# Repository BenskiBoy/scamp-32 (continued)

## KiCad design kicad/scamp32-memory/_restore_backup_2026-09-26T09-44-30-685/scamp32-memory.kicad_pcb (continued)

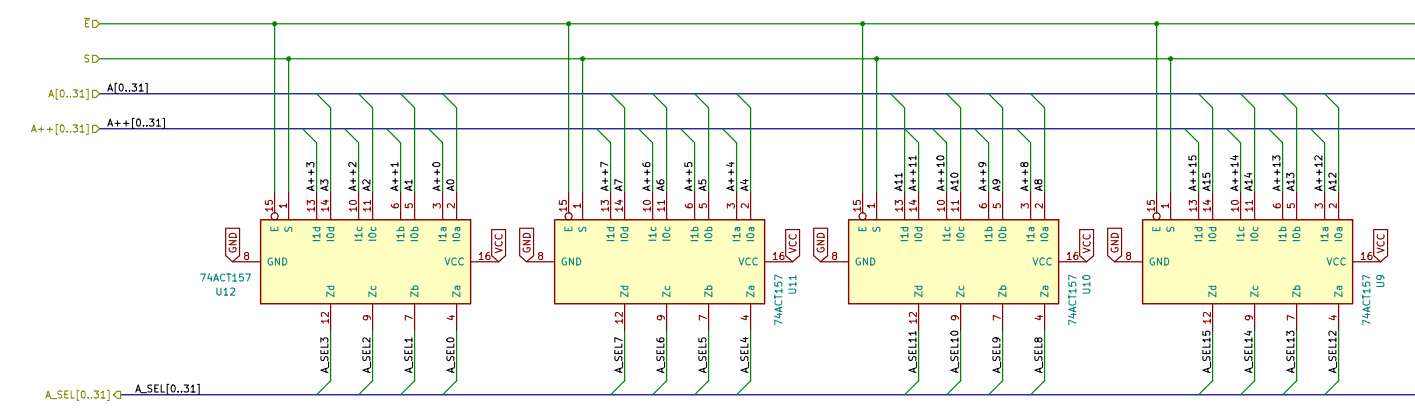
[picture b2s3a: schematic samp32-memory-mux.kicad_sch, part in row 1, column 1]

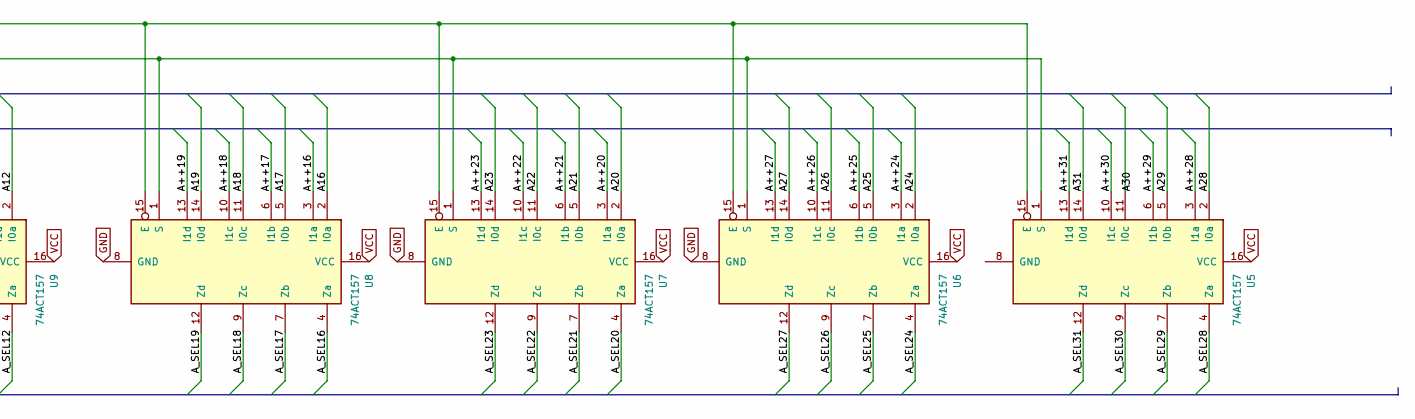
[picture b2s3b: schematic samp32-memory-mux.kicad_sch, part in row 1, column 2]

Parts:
U5, U6, U7, U8, U9, U10, U11, U12: 74ACT157; TSSOP-16_4.4x5mm_P0.65mm

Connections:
/A0: U12.2 (I0a); also elsewhere on the board
/A1: U12.5 (I0b); also elsewhere on the board
/A2: U12.11 (I0c); also elsewhere on the board
/A3: U12.14 (I0d); also elsewhere on the board
/A4: U11.2 (I0a); also elsewhere on the board
/A5: U11.5 (I0b); also elsewhere on the board
/A6: U11.11 (I0c); also elsewhere on the board
/A7: U11.14 (I0d); also elsewhere on the board
/A8: U10.2 (I0a); also elsewhere on the board
/A9: U10.5 (I0b); also elsewhere on the board
/A10: U10.11 (I0c); also elsewhere on the board
/A11: U10.13 (I1d); also elsewhere on the board
/A12: U9.2 (I0a); also elsewhere on the board
/A13: U9.5 (I0b); also elsewhere on the board
/A14: U9.11 (I0c); also elsewhere on the board
/A15: U9.14 (I0d); also elsewhere on the board
/A16: U8.2 (I0a); also elsewhere on the board
/A17: U8.5 (I0b); also elsewhere on the board
/A18: U8.11 (I0c); also elsewhere on the board
/A19: U8.14 (I0d); also elsewhere on the board
/A20: U7.2 (I0a); also elsewhere on the board
/A21: U7.5 (I0b); also elsewhere on the board
/A22: U7.11 (I0c); also elsewhere on the board
/A23: U7.14 (I0d); also elsewhere on the board
/A24: U6.2 (I0a); also elsewhere on the board
/A25: U6.5 (I0b); also elsewhere on the board
/A26: U6.11 (I0c); also elsewhere on the board
/A27: U6.14 (I0d); also elsewhere on the board
/A28: U5.2 (I0a); also elsewhere on the board
/A29: U5.5 (I0b); also elsewhere on the board
/A31: U5.14 (I0d); also elsewhere on the board
/samp32-memory-mux/A++0: U12.3 (I1a); also elsewhere on the board
/samp32-memory-mux/A++1: U12.6 (I1b); also elsewhere on the board
/samp32-memory-mux/A++2: U12.10 (I1c); also elsewhere on the board
/samp32-memory-mux/A++3: U12.13 (I1d); also elsewhere on the board
/samp32-memory-mux/A++4: U11.3 (I1a); also elsewhere on the board
/samp32-memory-mux/A++5: U11.6 (I1b); also elsewhere on the board
/samp32-memory-mux/A++6: U11.10 (I1c); also elsewhere on the board
/samp32-memory-mux/A++7: U11.13 (I1d); also elsewhere on the board
/samp32-memory-mux/A++8: U10.3 (I1a); also elsewhere on the board
/samp32-memory-mux/A++9: U10.6 (I1b); also elsewhere on the board
/samp32-memory-mux/A++10: U10.10 (I1c); also elsewhere on the board
/samp32-memory-mux/A++11: U10.14 (I0d); also elsewhere on the board
/samp32-memory-mux/A++12: U9.3 (I1a); also elsewhere on the board
/samp32-memory-mux/A++13: U9.6 (I1b); also elsewhere on the board
/samp32-memory-mux/A++14: U9.10 (I1c); also elsewhere on the board
/samp32-memory-mux/A++15: U9.13 (I1d); also elsewhere on the board
/samp32-memory-mux/A++16: U8.3 (I1a); also elsewhere on the board
/samp32-memory-mux/A++17: U8.6 (I1b); also elsewhere on the board
/samp32-memory-mux/A++18: U8.10 (I1c); also elsewhere on the board
/samp32-memory-mux/A++19: U8.13 (I1d); also elsewhere on the board
/samp32-memory-mux/A++20: U7.3 (I1a); also elsewhere on the board
/samp32-memory-mux/A++21: U7.6 (I1b); also elsewhere on the board
/samp32-memory-mux/A++22: U7.10 (I1c); also elsewhere on the board
/samp32-memory-mux/A++23: U7.13 (I1d); also elsewhere on the board
/samp32-memory-mux/A++24: U6.3 (I1a); also elsewhere on the board
/samp32-memory-mux/A++25: U6.6 (I1b); also elsewhere on the board
/samp32-memory-mux/A++26: U6.10 (I1c); also elsewhere on the board
/samp32-memory-mux/A++27: U6.13 (I1d); also elsewhere on the board
/samp32-memory-mux/A++28: U5.3 (I1a); also elsewhere on the board
/samp32-memory-mux/A++29: U5.6 (I1b); also elsewhere on the board
/samp32-memory-mux/A++30: U5.10 (I1c); also elsewhere on the board
/samp32-memory-mux/A++31: U5.13 (I1d); also elsewhere on the board
/samp32-memory-mux/A_SEL0: U12.4 (Za); also elsewhere on the board
/samp32-memory-mux/A_SEL1: U12.7 (Zb); also elsewhere on the board
/samp32-memory-mux/A_SEL2: U12.9 (Zc); also elsewhere on the board
/samp32-memory-mux/A_SEL3: U12.12 (Zd); also elsewhere on the board
/samp32-memory-mux/A_SEL4: U11.4 (Za); also elsewhere on the board
/samp32-memory-mux/A_SEL5: U11.7 (Zb); also elsewhere on the board
/samp32-memory-mux/A_SEL6: U11.9 (Zc); also elsewhere on the board
/samp32-memory-mux/A_SEL7: U11.12 (Zd); also elsewhere on the board
/samp32-memory-mux/A_SEL8: U10.4 (Za); also elsewhere on the board
/samp32-memory-mux/A_SEL9: U10.7 (Zb); also elsewhere on the board
/samp32-memory-mux/A_SEL10: U10.9 (Zc); also elsewhere on the board
/samp32-memory-mux/A_SEL11: U10.12 (Zd); also elsewhere on the board
/samp32-memory-mux/A_SEL12: U9.4 (Za); also elsewhere on the board
/samp32-memory-mux/A_SEL13: U9.7 (Zb); also elsewhere on the board
/samp32-memory-mux/A_SEL14: U9.9 (Zc); also elsewhere on the board
/samp32-memory-mux/A_SEL15: U9.12 (Zd); also elsewhere on the board
/samp32-memory-mux/A_SEL16: U8.4 (Za); also elsewhere on the board
/samp32-memory-mux/A_SEL17: U8.7 (Zb); also elsewhere on the board
/samp32-memory-mux/A_SEL18: U8.9 (Zc); also elsewhere on the board
/samp32-memory-mux/A_SEL19: U8.12 (Zd)
/samp32-memory-mux/A_SEL20: U7.4 (Za)
/samp32-memory-mux/A_SEL21: U7.7 (Zb)
/samp32-memory-mux/A_SEL22: U7.9 (Zc)
/samp32-memory-mux/A_SEL23: U7.12 (Zd)
/samp32-memory-mux/A_SEL24: U6.4 (Za)
/samp32-memory-mux/A_SEL25: U6.7 (Zb)
/samp32-memory-mux/A_SEL26: U6.9 (Zc)
/samp32-memory-mux/A_SEL27: U6.12 (Zd)
/samp32-memory-mux/A_SEL28: U5.4 (Za)
/samp32-memory-mux/A_SEL29: U5.7 (Zb)
/samp32-memory-mux/A_SEL30: U5.9 (Zc)
/samp32-memory-mux/A_SEL31: U5.12 (Zd)
/samp32-memory-mux/S: U5.1 (S), U6.1 (S), U7.1 (S), U8.1 (S), U9.1 (S), U10.1 (S), U11.1 (S), U12.1 (S); also elsewhere on the board
GND: U5.15 (E), U6.8 (GND), U6.15 (E), U7.8 (GND), U7.15 (E), U8.8 (GND), U8.15 (E), U9.8 (GND), U9.15 (E), U10.8 (GND), U10.15 (E), U11.8 (GND), U11.15 (E), U12.8 (GND), U12.15 (E); also elsewhere on the board
VCC: U5.16 (VCC), U6.16 (VCC), U7.16 (VCC), U8.16 (VCC), U9.16 (VCC), U10.16 (VCC), U11.16 (VCC), U12.16 (VCC); also elsewhere on the board

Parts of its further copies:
U13, U14, U15, U16, U17, U18, U19, U20: 74ACT157; TSSOP-16_4.4x5mm_P0.65mm

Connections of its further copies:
/A0: U13.2 (I0a); also elsewhere on the board
/A1: U13.5 (I0b); also elsewhere on the board
/A2: U13.11 (I0c); also elsewhere on the board
/A3: U13.14 (I0d); also elsewhere on the board
/A4: U14.2 (I0a); also elsewhere on the board
/A5: U14.5 (I0b); also elsewhere on the board
/A6: U14.11 (I0c); also elsewhere on the board
/A7: U14.14 (I0d); also elsewhere on the board
/A8: U15.2 (I0a); also elsewhere on the board
/A9: U15.5 (I0b); also elsewhere on the board
/A10: U15.11 (I0c); also elsewhere on the board
/A11: U15.13 (I1d); also elsewhere on the board
/A12: U16.2 (I0a); also elsewhere on the board
/A13: U16.5 (I0b); also elsewhere on the board
/A14: U16.11 (I0c); also elsewhere on the board
/A15: U16.14 (I0d); also elsewhere on the board
/A16: U17.2 (I0a); also elsewhere on the board
/A17: U17.5 (I0b); also elsewhere on the board
/A18: U17.11 (I0c); also elsewhere on the board
/A19: U17.14 (I0d); also elsewhere on the board
/A20: U18.2 (I0a); also elsewhere on the board
/A21: U18.5 (I0b); also elsewhere on the board
/A22: U18.11 (I0c); also elsewhere on the board
/A23: U18.14 (I0d); also elsewhere on the board
/A24: U19.2 (I0a); also elsewhere on the board
/A25: U19.5 (I0b); also elsewhere on the board
/A26: U19.11 (I0c); also elsewhere on the board
/A27: U19.14 (I0d); also elsewhere on the board
/A28: U20.2 (I0a); also elsewhere on the board
/A29: U20.5 (I0b); also elsewhere on the board
/A31: U20.14 (I0d); also elsewhere on the board
/samp32-memory-mux1/A_SEL19: U17.12 (Zd)
/samp32-memory-mux1/A_SEL20: U18.4 (Za)
/samp32-memory-mux1/A_SEL21: U18.7 (Zb)
/samp32-memory-mux1/A_SEL22: U18.9 (Zc)
/samp32-memory-mux1/A_SEL23: U18.12 (Zd)
/samp32-memory-mux1/A_SEL24: U19.4 (Za)
/samp32-memory-mux1/A_SEL25: U19.7 (Zb)
/samp32-memory-mux1/A_SEL26: U19.9 (Zc)
/samp32-memory-mux1/A_SEL27: U19.12 (Zd)
/samp32-memory-mux1/A_SEL28: U20.4 (Za)
/samp32-memory-mux1/A_SEL29: U20.7 (Zb)
/samp32-memory-mux1/A_SEL30: U20.9 (Zc)
/samp32-memory-mux1/A_SEL31: U20.12 (Zd)
/samp32-memory-mux1/S: U13.1 (S), U14.1 (S), U15.1 (S), U16.1 (S), U17.1 (S), U18.1 (S), U19.1 (S), U20.1 (S); also elsewhere on the board
/samp32-memory-mux/A++0: U13.3 (I1a); also elsewhere on the board
/samp32-memory-mux/A++1: U13.6 (I1b); also elsewhere on the board
/samp32-memory-mux/A++2: U13.10 (I1c); also elsewhere on the board
/samp32-memory-mux/A++3: U13.13 (I1d); also elsewhere on the board
/samp32-memory-mux/A++4: U14.3 (I1a); also elsewhere on the board
/samp32-memory-mux/A++5: U14.6 (I1b); also elsewhere on the board
/samp32-memory-mux/A++6: U14.10 (I1c); also elsewhere on the board
/samp32-memory-mux/A++7: U14.13 (I1d); also elsewhere on the board
/samp32-memory-mux/A++8: U15.3 (I1a); also elsewhere on the board
/samp32-memory-mux/A++9: U15.6 (I1b); also elsewhere on the board
/samp32-memory-mux/A++10: U15.10 (I1c); also elsewhere on the board
/samp32-memory-mux/A++11: U15.14 (I0d); also elsewhere on the board
/samp32-memory-mux/A++12: U16.3 (I1a); also elsewhere on the board
/samp32-memory-mux/A++13: U16.6 (I1b); also elsewhere on the board
/samp32-memory-mux/A++14: U16.10 (I1c); also elsewhere on the board
/samp32-memory-mux/A++15: U16.13 (I1d); also elsewhere on the board
/samp32-memory-mux/A++16: U17.3 (I1a); also elsewhere on the board
/samp32-memory-mux/A++17: U17.6 (I1b); also elsewhere on the board
/samp32-memory-mux/A++18: U17.10 (I1c); also elsewhere on the board
/samp32-memory-mux/A++19: U17.13 (I1d); also elsewhere on the board
/samp32-memory-mux/A++20: U18.3 (I1a); also elsewhere on the board
/samp32-memory-mux/A++21: U18.6 (I1b); also elsewhere on the board
/samp32-memory-mux/A++22: U18.10 (I1c); also elsewhere on the board
/samp32-memory-mux/A++23: U18.13 (I1d); also elsewhere on the board
/samp32-memory-mux/A++24: U19.3 (I1a); also elsewhere on the board
/samp32-memory-mux/A++25: U19.6 (I1b); also elsewhere on the board
/samp32-memory-mux/A++26: U19.10 (I1c); also elsewhere on the board
/samp32-memory-mux/A++27: U19.13 (I1d); also elsewhere on the board
/samp32-memory-mux/A++28: U20.3 (I1a); also elsewhere on the board
/samp32-memory-mux/A++29: U20.6 (I1b); also elsewhere on the board
/samp32-memory-mux/A++30: U20.10 (I1c); also elsewhere on the board
/samp32-memory-mux/A++31: U20.13 (I1d); also elsewhere on the board
/samp32-memory-mux/A_SEL0: U13.4 (Za); also elsewhere on the board
/samp32-memory-mux/A_SEL1: U13.7 (Zb); also elsewhere on the board
/samp32-memory-mux/A_SEL2: U13.9 (Zc); also elsewhere on the board
/samp32-memory-mux/A_SEL3: U13.12 (Zd); also elsewhere on the board
/samp32-memory-mux/A_SEL4: U14.4 (Za); also elsewhere on the board
/samp32-memory-mux/A_SEL5: U14.7 (Zb); also elsewhere on the board
/samp32-memory-mux/A_SEL6: U14.9 (Zc); also elsewhere on the board
/samp32-memory-mux/A_SEL7: U14.12 (Zd); also elsewhere on the board
/samp32-memory-mux/A_SEL8: U15.4 (Za); also elsewhere on the board
/samp32-memory-mux/A_SEL9: U15.7 (Zb); also elsewhere on the board
/samp32-memory-mux/A_SEL10: U15.9 (Zc); also elsewhere on the board
/samp32-memory-mux/A_SEL11: U15.12 (Zd); also elsewhere on the board
/samp32-memory-mux/A_SEL12: U16.4 (Za); also elsewhere on the board
/samp32-memory-mux/A_SEL13: U16.7 (Zb); also elsewhere on the board
/samp32-memory-mux/A_SEL14: U16.9 (Zc); also elsewhere on the board
/samp32-memory-mux/A_SEL15: U16.12 (Zd); also elsewhere on the board
/samp32-memory-mux/A_SEL16: U17.4 (Za); also elsewhere on the board
/samp32-memory-mux/A_SEL17: U17.7 (Zb); also elsewhere on the board
/samp32-memory-mux/A_SEL18: U17.9 (Zc); also elsewhere on the board
GND: U13.8 (GND), U13.15 (E), U14.8 (GND), U14.15 (E), U15.8 (GND), U15.15 (E), U16.8 (GND), U16.15 (E), U17.8 (GND), U17.15 (E), U18.8 (GND), U18.15 (E), U19.8 (GND), U19.15 (E), U20.15 (E); also elsewhere on the board
VCC: U13.16 (VCC), U14.16 (VCC), U15.16 (VCC), U16.16 (VCC), U17.16 (VCC), U18.16 (VCC), U19.16 (VCC), U20.16 (VCC); also elsewhere on the board

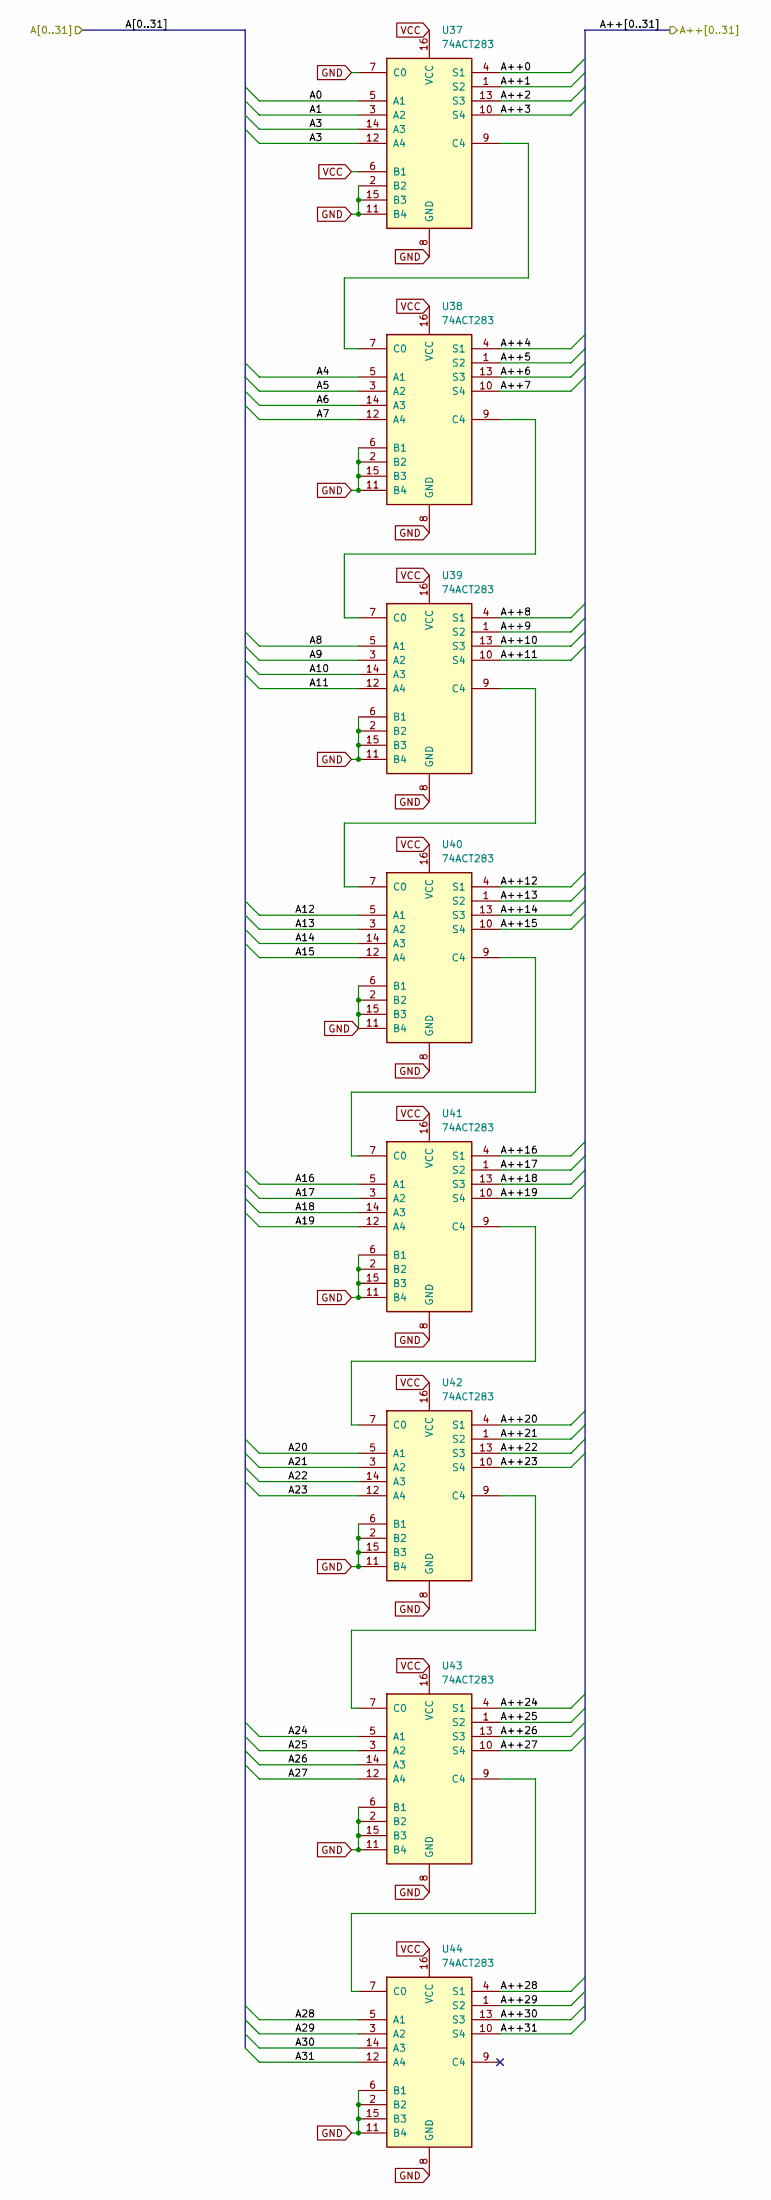
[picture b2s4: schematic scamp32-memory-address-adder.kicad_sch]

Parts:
U37, U38, U39, U40, U41, U42, U43, U44: 74ACT283; TSSOP-16_4.4x5mm_P0.65mm

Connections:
/A0: U37.5 (A1); also elsewhere on the board
/A1: U37.3 (A2); also elsewhere on the board
/A3: U37.12 (A4), U37.14 (A3); also elsewhere on the board
/A4: U38.5 (A1); also elsewhere on the board
/A5: U38.3 (A2); also elsewhere on the board
/A6: U38.14 (A3); also elsewhere on the board
/A7: U38.12 (A4); also elsewhere on the board
/A8: U39.5 (A1); also elsewhere on the board
/A9: U39.3 (A2); also elsewhere on the board
/A10: U39.14 (A3); also elsewhere on the board
/A11: U39.12 (A4); also elsewhere on the board
/A12: U40.5 (A1); also elsewhere on the board
/A13: U40.3 (A2); also elsewhere on the board
/A14: U40.14 (A3); also elsewhere on the board
/A15: U40.12 (A4); also elsewhere on the board
/A16: U41.5 (A1); also elsewhere on the board
/A17: U41.3 (A2); also elsewhere on the board
/A18: U41.14 (A3); also elsewhere on the board
/A19: U41.12 (A4); also elsewhere on the board
/A20: U42.5 (A1); also elsewhere on the board
/A21: U42.3 (A2); also elsewhere on the board
/A22: U42.14 (A3); also elsewhere on the board
/A23: U42.12 (A4); also elsewhere on the board
/A24: U43.5 (A1); also elsewhere on the board
/A25: U43.3 (A2); also elsewhere on the board
/A26: U43.14 (A3); also elsewhere on the board
/A27: U43.12 (A4); also elsewhere on the board
/A28: U44.5 (A1); also elsewhere on the board
/A29: U44.3 (A2); also elsewhere on the board
/A30: U44.14 (A3); also elsewhere on the board
/A31: U44.12 (A4); also elsewhere on the board
/samp32-memory-mux/A++0: U37.4 (S1); also elsewhere on the board
/samp32-memory-mux/A++1: U37.1 (S2); also elsewhere on the board
/samp32-memory-mux/A++2: U37.13 (S3); also elsewhere on the board
/samp32-memory-mux/A++3: U37.10 (S4); also elsewhere on the board
/samp32-memory-mux/A++4: U38.4 (S1); also elsewhere on the board
/samp32-memory-mux/A++5: U38.1 (S2); also elsewhere on the board
/samp32-memory-mux/A++6: U38.13 (S3); also elsewhere on the board
/samp32-memory-mux/A++7: U38.10 (S4); also elsewhere on the board
/samp32-memory-mux/A++8: U39.4 (S1); also elsewhere on the board
/samp32-memory-mux/A++9: U39.1 (S2); also elsewhere on the board
/samp32-memory-mux/A++10: U39.13 (S3); also elsewhere on the board
/samp32-memory-mux/A++11: U39.10 (S4); also elsewhere on the board
/samp32-memory-mux/A++12: U40.4 (S1); also elsewhere on the board
/samp32-memory-mux/A++13: U40.1 (S2); also elsewhere on the board
/samp32-memory-mux/A++14: U40.13 (S3); also elsewhere on the board
/samp32-memory-mux/A++15: U40.10 (S4); also elsewhere on the board
/samp32-memory-mux/A++16: U41.4 (S1); also elsewhere on the board
/samp32-memory-mux/A++17: U41.1 (S2); also elsewhere on the board
/samp32-memory-mux/A++18: U41.13 (S3); also elsewhere on the board
/samp32-memory-mux/A++19: U41.10 (S4); also elsewhere on the board
/samp32-memory-mux/A++20: U42.4 (S1); also elsewhere on the board
/samp32-memory-mux/A++21: U42.1 (S2); also elsewhere on the board
/samp32-memory-mux/A++22: U42.13 (S3); also elsewhere on the board
/samp32-memory-mux/A++23: U42.10 (S4); also elsewhere on the board
/samp32-memory-mux/A++24: U43.4 (S1); also elsewhere on the board
/samp32-memory-mux/A++25: U43.1 (S2); also elsewhere on the board
/samp32-memory-mux/A++26: U43.13 (S3); also elsewhere on the board
/samp32-memory-mux/A++27: U43.10 (S4); also elsewhere on the board
/samp32-memory-mux/A++28: U44.4 (S1); also elsewhere on the board
/samp32-memory-mux/A++29: U44.1 (S2); also elsewhere on the board
/samp32-memory-mux/A++30: U44.13 (S3); also elsewhere on the board
/samp32-memory-mux/A++31: U44.10 (S4); also elsewhere on the board
GND: U37.2 (B2), U37.7 (C0), U37.8 (GND), U37.11 (B4), U37.15 (B3), U38.2 (B2), U38.6 (B1), U38.8 (GND), U38.11 (B4), U38.15 (B3), U39.2 (B2), U39.6 (B1), U39.8 (GND), U39.11 (B4), U39.15 (B3), U40.2 (B2), U40.6 (B1), U40.8 (GND), U40.11 (B4), U40.15 (B3), U41.2 (B2), U41.6 (B1), U41.8 (GND), U41.11 (B4), U41.15 (B3), U42.2 (B2), U42.6 (B1), U42.8 (GND), U42.11 (B4), U42.15 (B3), U43.2 (B2), U43.6 (B1), U43.8 (GND), U43.11 (B4), U43.15 (B3), U44.2 (B2), U44.6 (B1), U44.8 (GND), U44.11 (B4), U44.15 (B3); also elsewhere on the board
unnamed: U37.9 (C4), U38.7 (C0)
unnamed: U38.9 (C4), U39.7 (C0)
unnamed: U39.9 (C4), U40.7 (C0)
unnamed: U40.9 (C4), U41.7 (C0)
unnamed: U41.9 (C4), U42.7 (C0)
unnamed: U42.9 (C4), U43.7 (C0)
unnamed: U43.9 (C4), U44.7 (C0)
VCC: U37.6 (B1), U37.16 (VCC), U38.16 (VCC), U39.16 (VCC), U40.16 (VCC), U41.16 (VCC), U43.16 (VCC), U44.16 (VCC); also elsewhere on the board

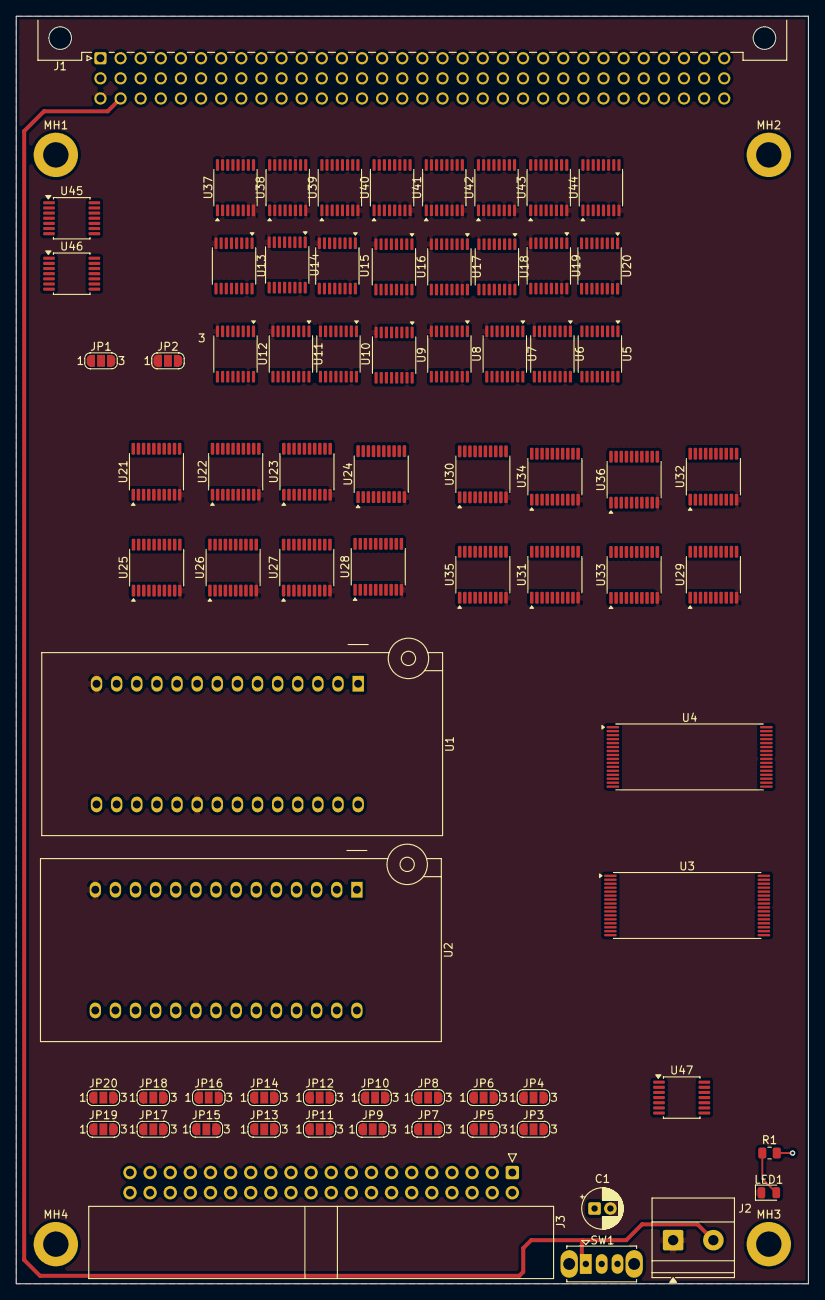
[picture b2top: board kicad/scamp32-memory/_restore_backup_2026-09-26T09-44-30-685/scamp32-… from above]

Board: 4 copper layers, 100.0 x 160.0 mm, 78 parts (0 on the bottom side), 208 nets.

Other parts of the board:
MH1, MH2, MH3, MH4: MountingHole_3.2mm_M3_DIN965_Pad

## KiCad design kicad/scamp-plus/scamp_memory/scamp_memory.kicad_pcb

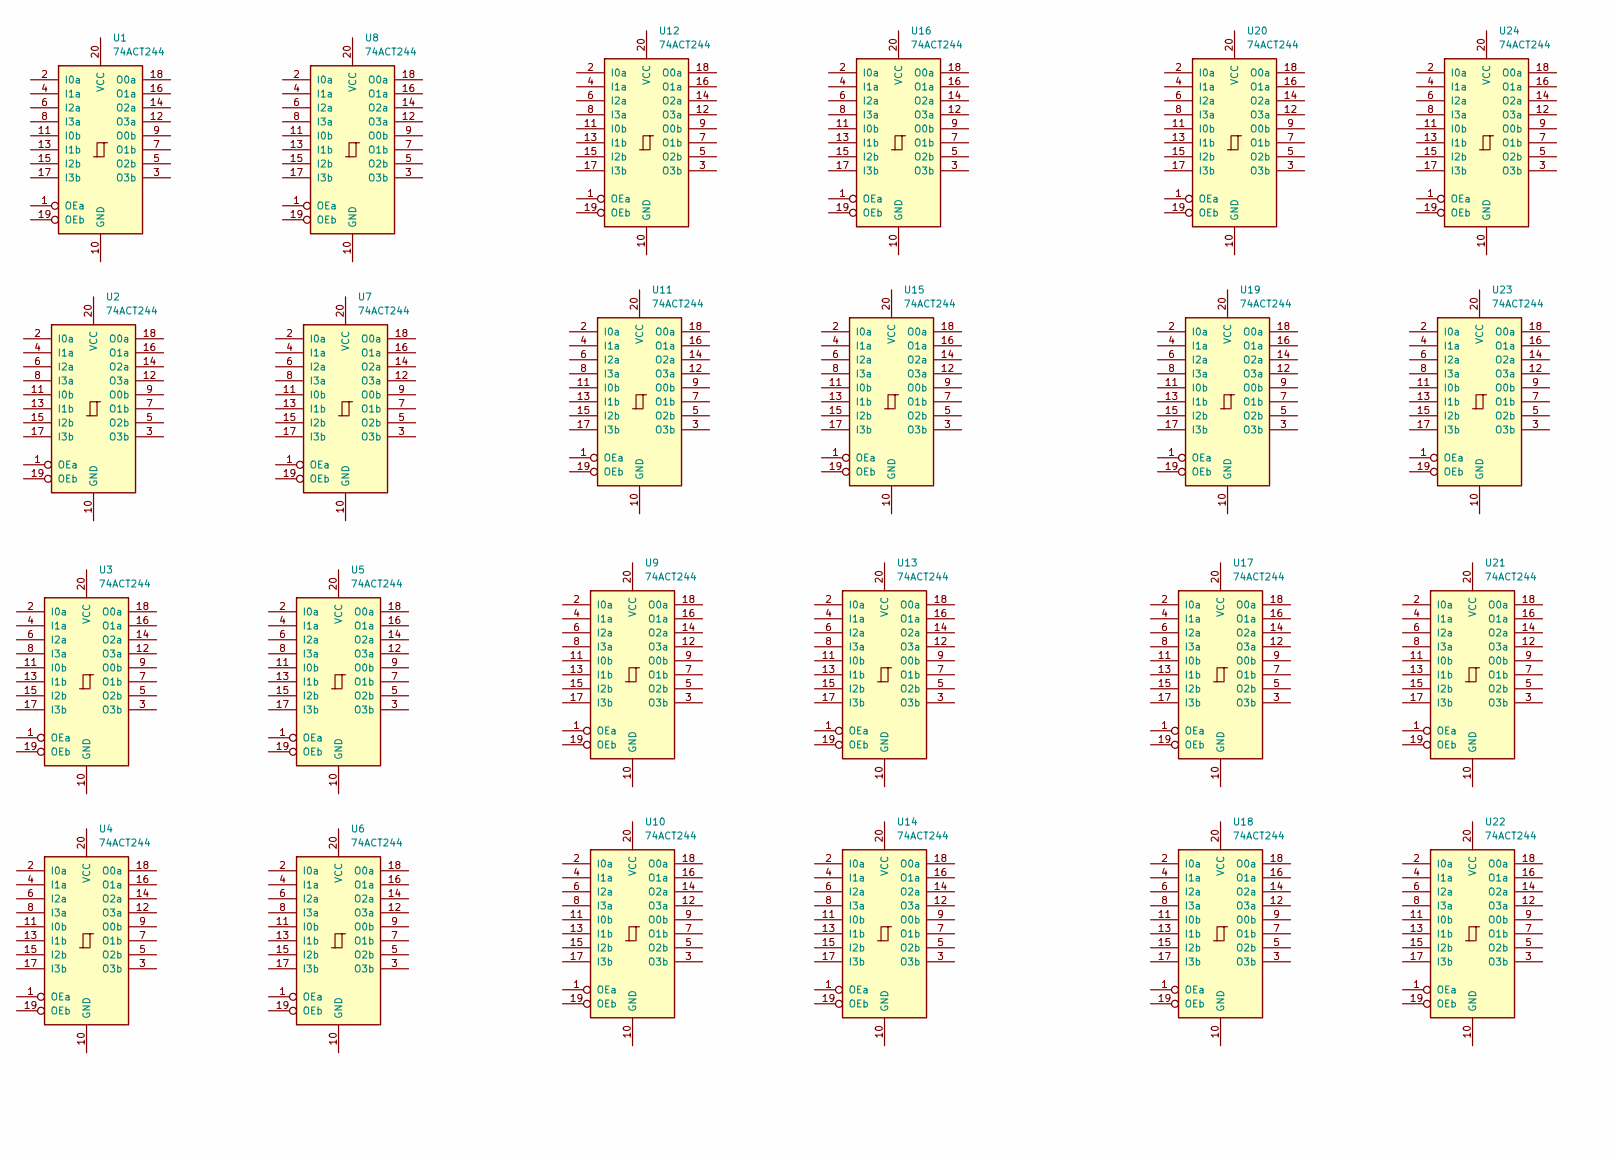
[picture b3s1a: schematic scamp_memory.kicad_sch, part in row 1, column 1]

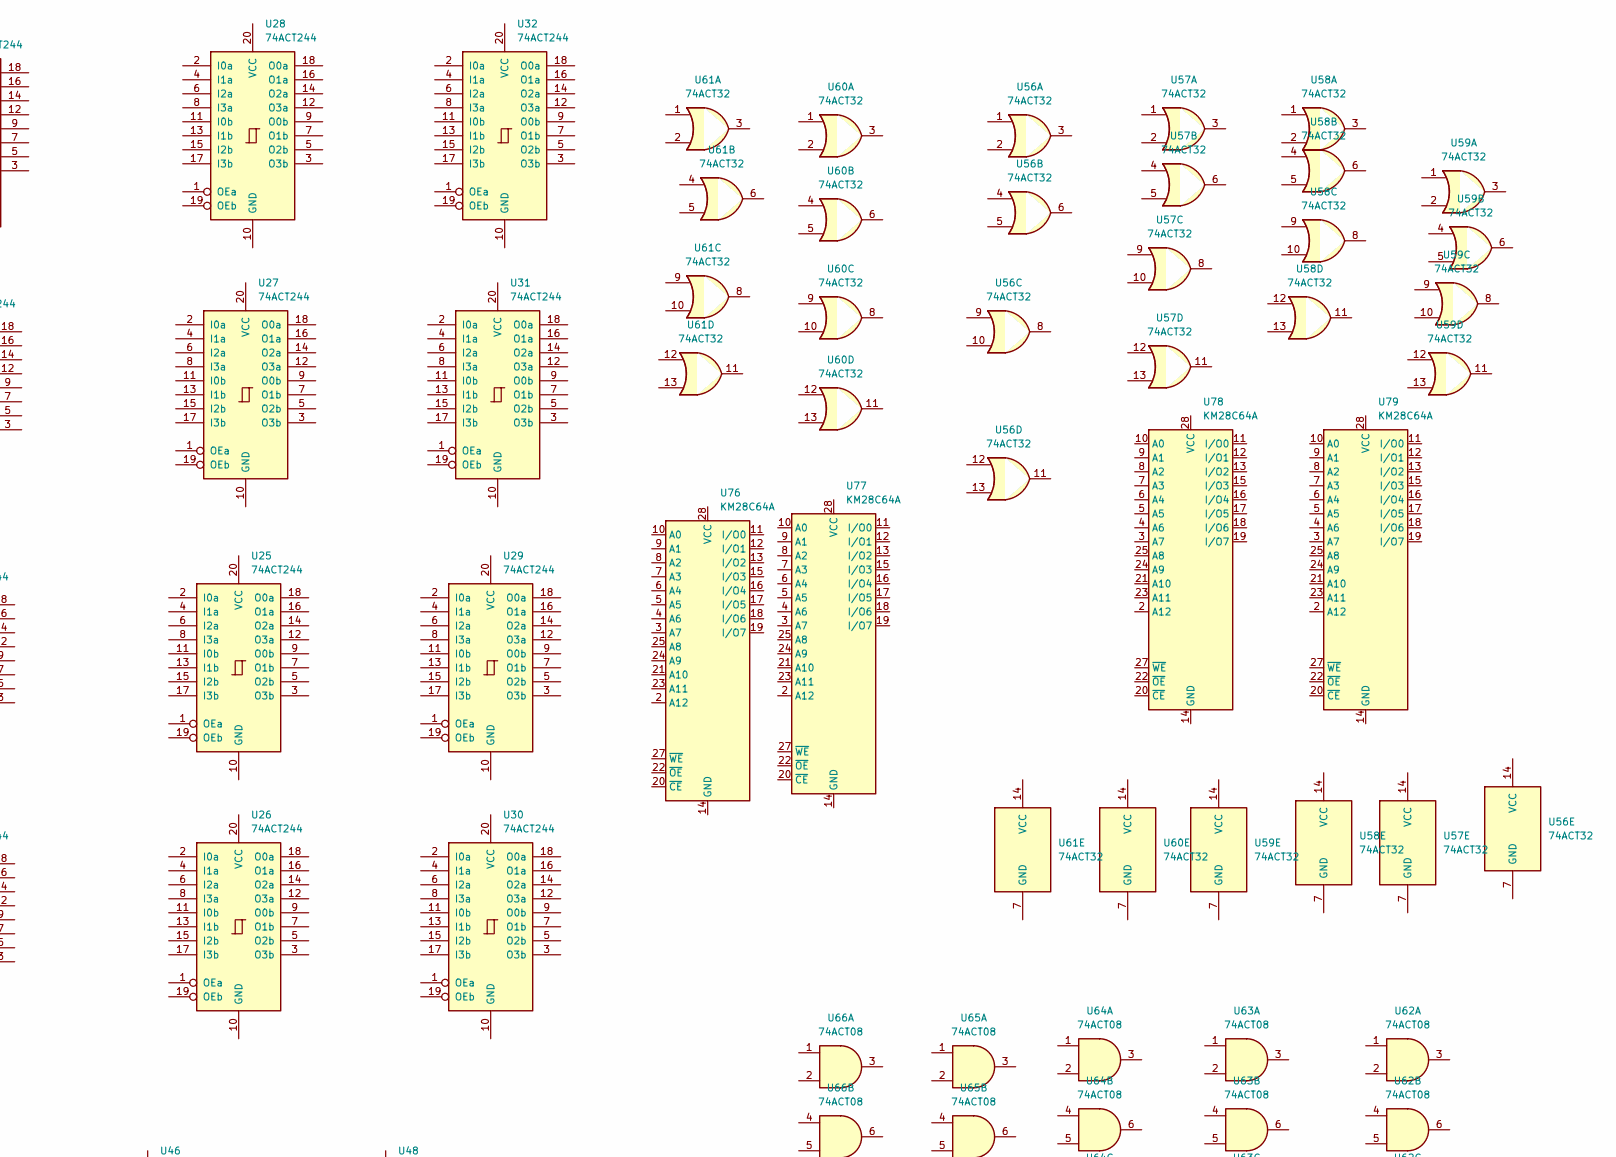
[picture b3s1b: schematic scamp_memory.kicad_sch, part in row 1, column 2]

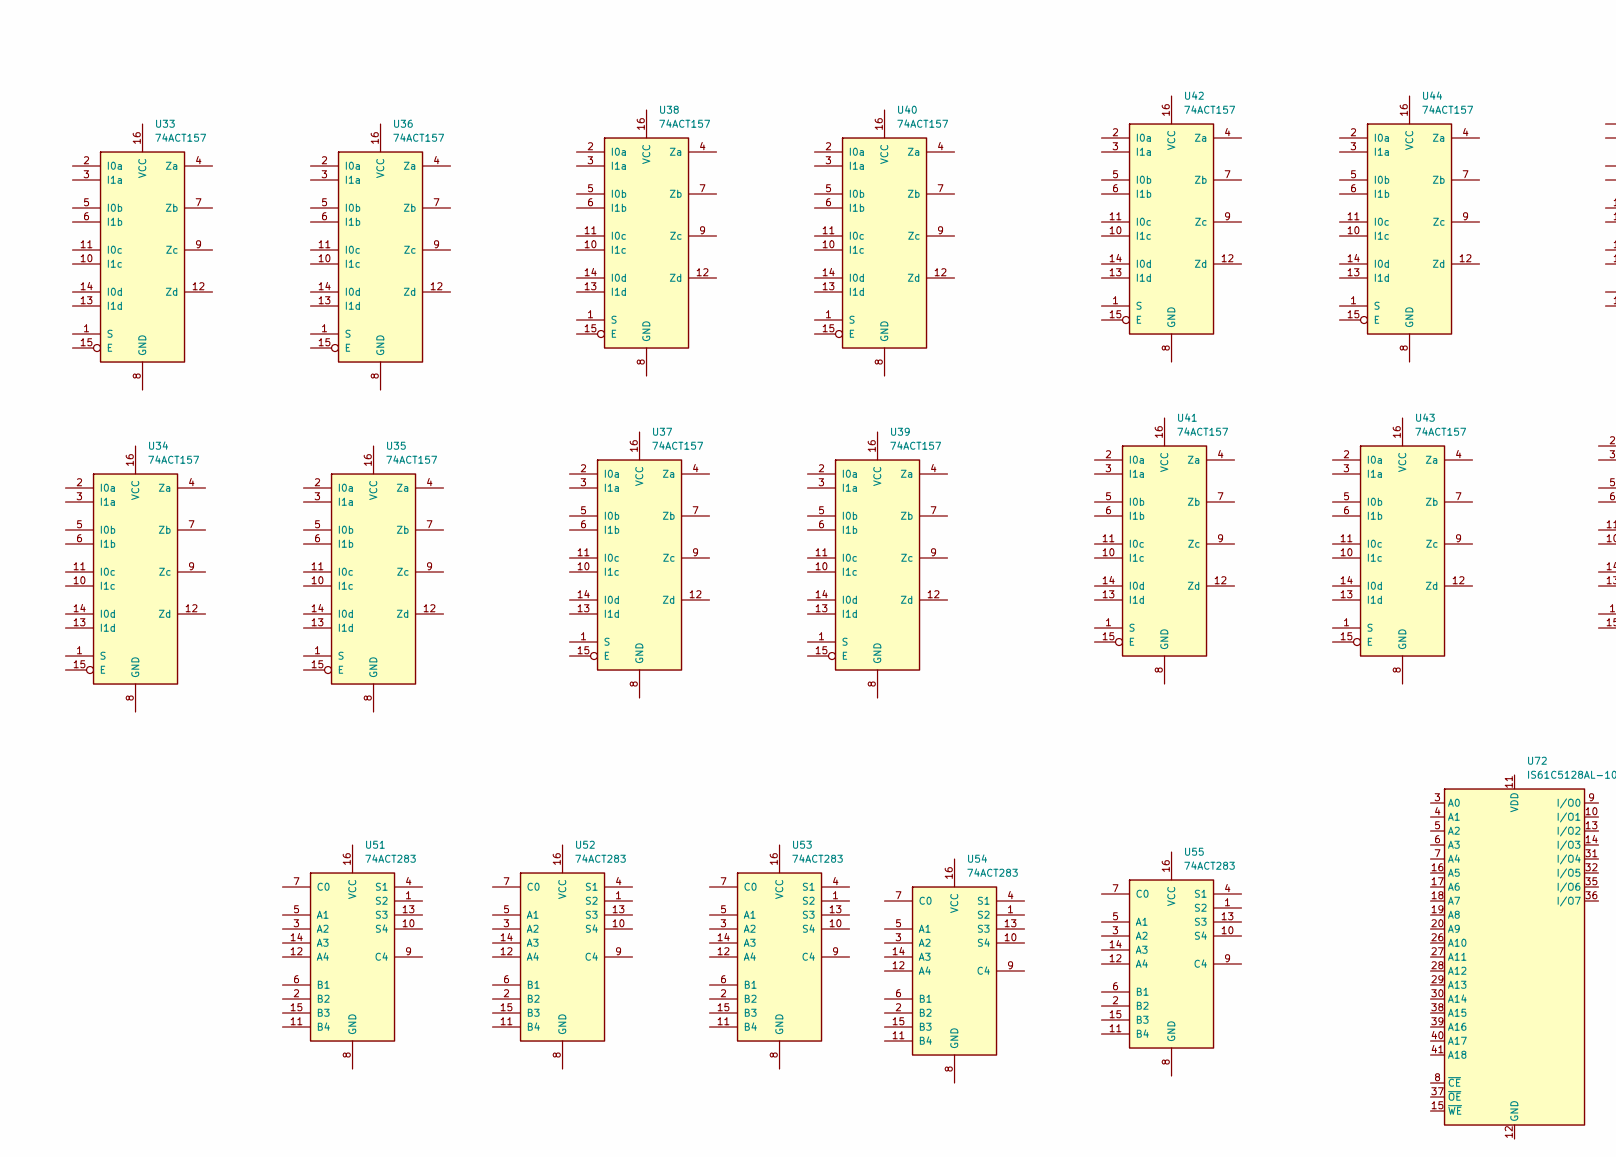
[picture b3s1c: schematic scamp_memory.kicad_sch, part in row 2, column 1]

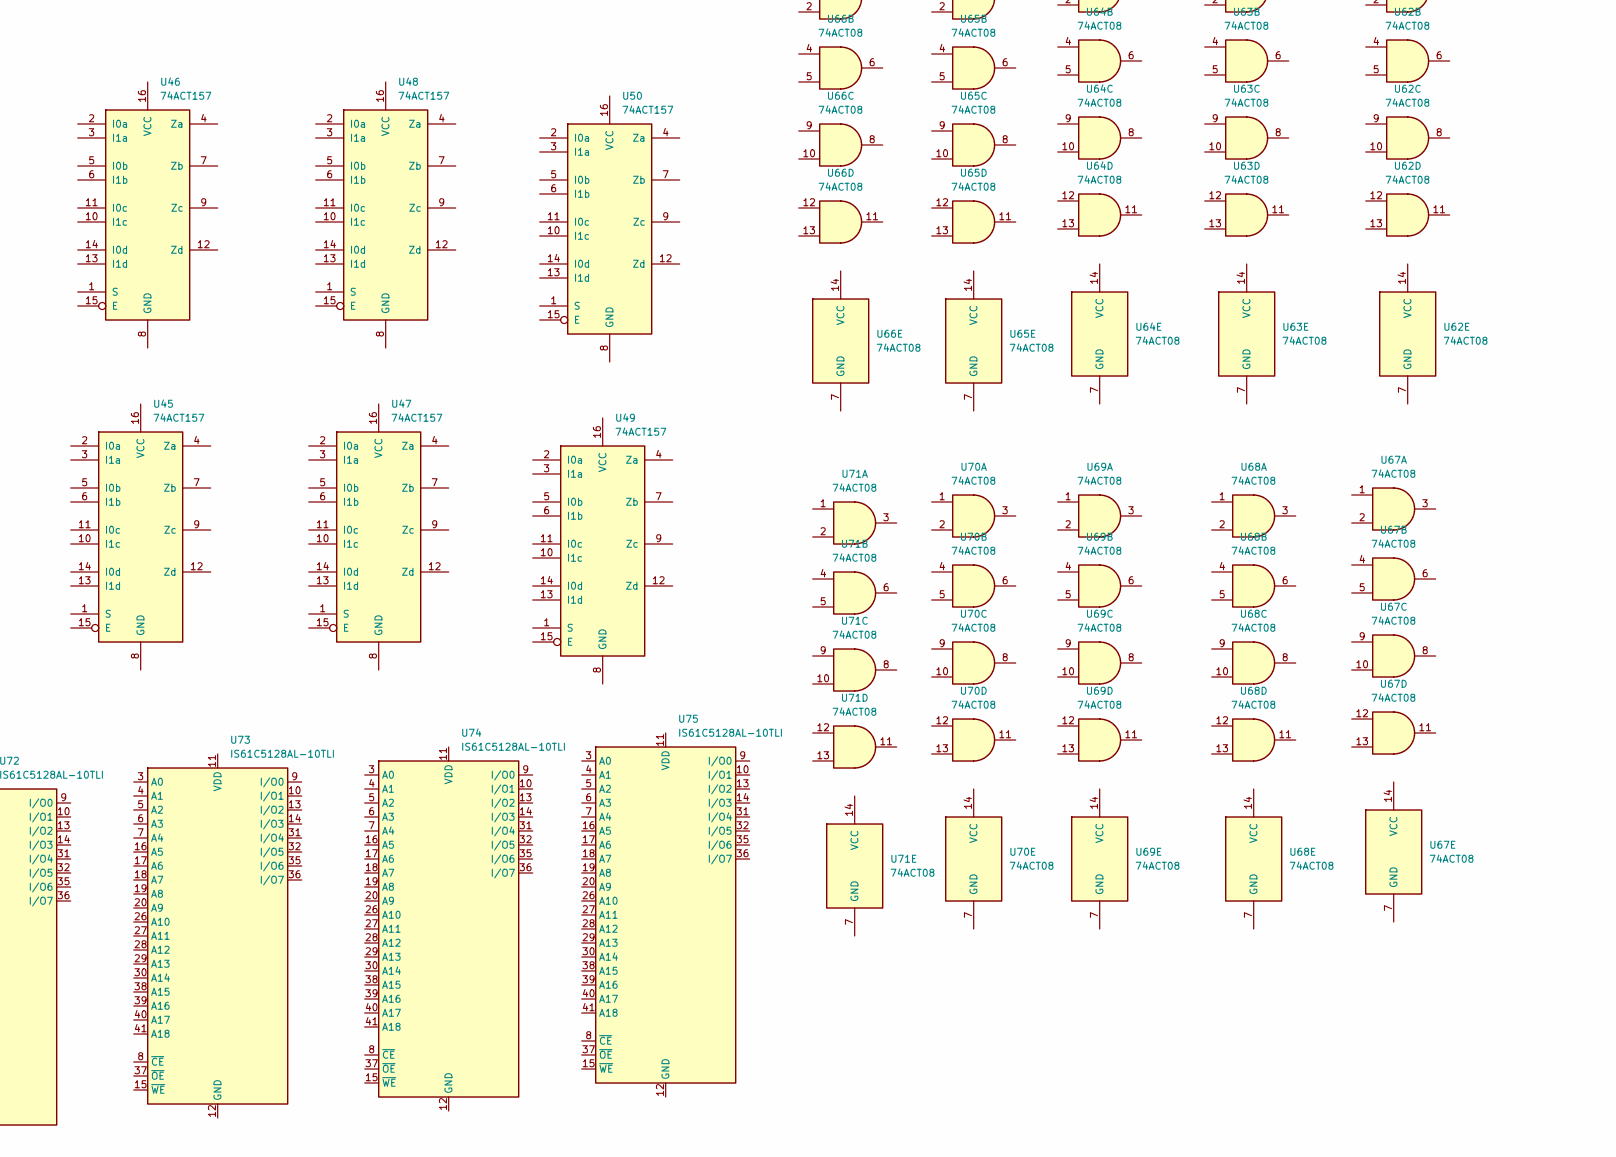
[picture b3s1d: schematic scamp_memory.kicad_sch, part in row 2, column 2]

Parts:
U1, U2, U3, U4, U5, U6, U7, U8, U9, U10, U11, U12, U13, U14, U15, U16, U17, U18, U19, U20, U21, U22, U23, U24, U25, U26, U27, U28, U29, U30, U31, U32: 74ACT244; SOIC-20W_7.5x12.8mm_P1.27mm
U33, U34, U35, U36, U37, U38, U39, U40, U41, U42, U43, U44, U45, U46, U47, U48, U49, U50: 74ACT157; SOIC-16_3.9x9.9mm_P1.27mm
U51, U52, U53, U54, U55: 74ACT283; SOIC-16_3.9x9.9mm_P1.27mm
U56, U57, U58, U59, U60, U61: 74ACT32; SOIC-14_3.9x8.7mm_P1.27mm
U62, U63, U64, U65, U66, U67, U68, U69, U70, U71: 74ACT08; SOIC-14_3.9x8.7mm_P1.27mm
U72, U73, U74, U75: IS61C5128AL-10TLI; TSOP-II-44_10.16x18.41mm_P0.8mm
U76, U77, U78, U79: KM28C64A; DIP-28_W15.24mm

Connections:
unnamed: U72.12 (GND), U72.34 (GND)
unnamed: U72.11 (VDD), U72.33 (VDD)
unnamed: U73.12 (GND), U73.34 (GND)
unnamed: U73.11 (VDD), U73.33 (VDD)
unnamed: U74.12 (GND), U74.34 (GND)
unnamed: U74.11 (VDD), U74.33 (VDD)
unnamed: U75.12 (GND), U75.34 (GND)
unnamed: U75.11 (VDD), U75.33 (VDD)

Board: 2 copper layers, 79 parts (0 on the bottom side), 8 nets, no tracks yet.
